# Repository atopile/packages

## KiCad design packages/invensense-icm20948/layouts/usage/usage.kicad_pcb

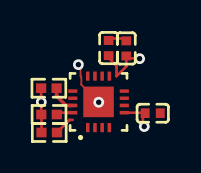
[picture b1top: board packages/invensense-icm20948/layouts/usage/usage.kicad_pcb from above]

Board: 2 copper layers, 7 parts (0 on the bottom side), 7 nets.

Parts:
C1, C3: 1±10.0%F; C0402
C2: {8.999..1.1}F; C0402
R1, R2, R3: 10000±1.0%Ω; R0402
U1: QFN-24_L3.0-W3.0-P0.40-BL-EP

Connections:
RESV: U1.19, U1.20
SCL: R2.2, U1.23
SDA: R3.2, U1.24
hv: C3.1, R1.1, R2.1, R3.1, U1.8
lv: C1.2, C2.2, C3.2, U1.9, U1.18, U1.25
nCS: R1.2, U1.22
power_core_filter-power-hv: C1.1, C2.1, U1.13

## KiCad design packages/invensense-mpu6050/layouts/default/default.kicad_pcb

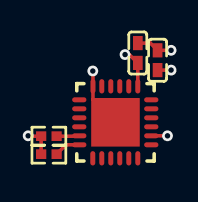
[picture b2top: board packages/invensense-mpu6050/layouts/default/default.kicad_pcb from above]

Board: 2 copper layers, 5 parts (0 on the bottom side), 5 nets.

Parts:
C1, C2: 1±10.0%F; C0402
R1, R2: 10000±1.0%Ω; R0402
U1: QFN-24_L4.0-W4.0-P0.50-BL-EP2.7

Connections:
SCL: R1.1, U1.23
SDA: R2.1, U1.24
decoupling_caps[0]-power-hv: C1.1, U1.13
hv: C2.1, R1.2, R2.2, U1.8
lv: C1.2, C2.2, U1.9, U1.18, U1.25

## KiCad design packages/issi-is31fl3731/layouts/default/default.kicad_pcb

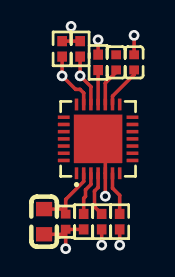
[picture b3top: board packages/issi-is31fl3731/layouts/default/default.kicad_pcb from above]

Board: 2 copper layers, 11 parts (0 on the bottom side), 10 nets.

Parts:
C1, C4, C5: 1±10.0%F; C0402
C2: {8.999..1.1}F; C0603
R1: 20000±1.0%Ω; R0402
R2, R3, R6: 10000±1.0%Ω; R0402
R4, R5: 4700±1.0%Ω; R0402
U1: QFN-28_L4.0-W4.0-P0.40-BL-EP

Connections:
AD: R2.1, U1.18
INTB: R3.1, U1.4
R_EXT: R1.1, U1.6
SCL: R4.1, U1.20
SDA: R5.1, U1.19
SDB: R6.1, U1.3
decoupling_capacitor_small-power-hv: C2.1, C4.1, R3.2, R4.2, R5.2, U1.2
filter_capacitor-power-hv: C5.1, U1.16
filter_capacitor-power-lv: C2.2, C4.2, C5.2, R1.2, R2.2, R6.2, U1.5, U1.29
lv: C1.2, U1.17

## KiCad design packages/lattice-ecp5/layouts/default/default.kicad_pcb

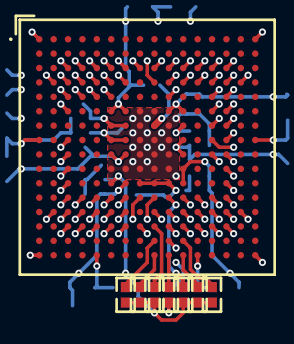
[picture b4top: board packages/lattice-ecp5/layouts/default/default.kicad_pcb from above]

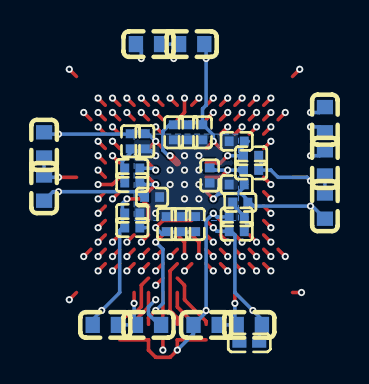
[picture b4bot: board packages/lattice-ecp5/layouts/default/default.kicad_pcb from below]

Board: 4 copper layers, 41 parts (33 on the bottom side), 17 nets.

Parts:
C1, C4, C5, C6, C7, C8, C9, C10, C24, C25, C26: 0F; C0603
C2, C3, C11, C12, C13, C14, C15, C16, C17, C18, C19, C20, C21, C22, C23, C27, C28, C29, C30, C31, C32: 0F; C0402
L1: L0402
R1, R2, R3, R4, R5, R6, R7: 4700Ω; R0402
U1: CABGA-256_L14.0-W14.0-R16-C16-P0.80-TL

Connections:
DONE: R3.1, U1.P9
GND: C1.2, C2.1, C3.1, C4.2, C5.2, C6.2, C7.2, C8.2, C9.2, C10.2, C11.2, C12.2, C13.2, C14.2, C15.2, C16.2, C17.2, C18.2, C19.2, C20.2, C21.2, C22.2, C23.2, C24.2, C25.2, C26.2, C27.1, C28.1, C29.1, C30.1, C31.1, C32.1, R7.2, U1.A1, U1.A16, U1.D2, U1.D15, U1.F8, U1.F9, U1.G8, U1.G10, U1.H1, U1.H8, U1.H9, U1.H10, U1.H16, U1.J8, U1.J9, U1.J10, U1.K6, U1.K7, U1.K8, U1.K9, U1.K10, U1.N2, U1.N15, U1.T1, U1.T5, U1.T12, U1.T16
INITN: R2.1, U1.T9
PROGRAMN: R1.1, U1.R9
TCK: R7.1, U1.T10
TDI: R4.1, U1.R11
TDO: R6.1, U1.M10
TMS: R5.1, U1.T11
hv: C1.1, C2.2, C3.2, L1.2, U1.G11, U1.L7
power_core-hv: C24.1, C25.1, C26.1, C27.2, C28.2, C29.2, C30.2, C31.2, C32.2, U1.G6, U1.G7, U1.G9, U1.L8, U1.L9, U1.L10
power_vccio[0]-hv: C4.1, C11.1, C12.1, U1.F6, U1.F7
power_vccio[1]-hv: C5.1, C13.1, C14.1, U1.F10, U1.F11
power_vccio[2]-hv: C6.1, C15.1, C16.1, U1.H11, U1.J11
power_vccio[3]-hv: C7.1, C17.1, C18.1, U1.K11, U1.L11
power_vccio[6]-hv: C8.1, C19.1, C20.1, U1.J6, U1.J7
power_vccio[7]-hv: C9.1, C21.1, C22.1, U1.H6, U1.H7
power_vccio[8]-hv: C10.1, C23.1, R1.2, R2.2, R3.2, R4.2, R5.2, R6.2, U1.L6

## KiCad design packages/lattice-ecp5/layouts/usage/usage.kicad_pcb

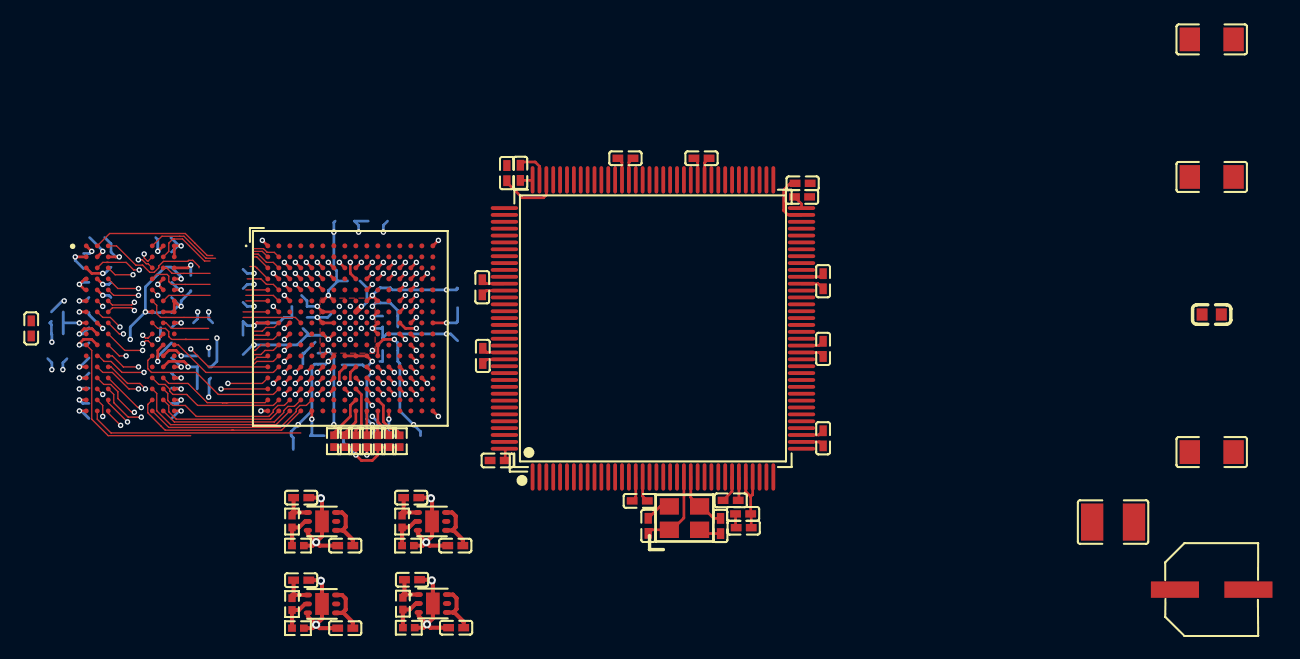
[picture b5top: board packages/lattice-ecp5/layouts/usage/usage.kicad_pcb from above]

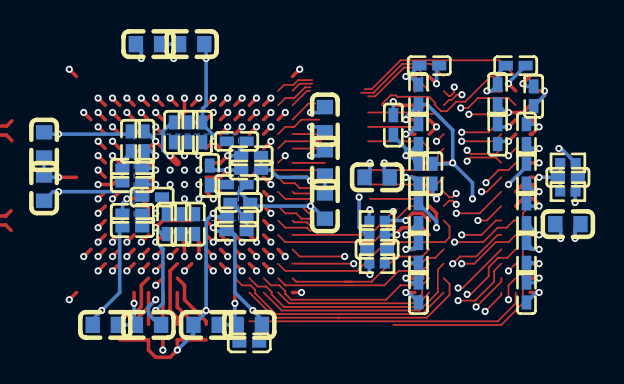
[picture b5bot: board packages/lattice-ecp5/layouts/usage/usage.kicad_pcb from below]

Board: 4 copper layers, 116 parts (60 on the bottom side), 64 nets.

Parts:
C1, C4, C5, C6, C7, C8, C9, C10, C24, C25, C26, C61, C67, C68: 10µF ±20% 6.3V X5R; C0603
C2, C3, C27, C28, C29, C30, C31, C32, C65, C66, C69, C70, C71, C72, C73, C74, C75, C76, C77, C78, C79, C80, C81, C82, C83, C84, C85, C86: 100nF ±10% 6.3V X7R; C0402
C11, C12, C13, C14, C15, C16, C17, C18, C19, C20, C21, C22, C23: 100nF ±10% 10V X5R; C0402
C33, C34, C35, C36, C37, C38, C39, C40, C57: 1µF ±10% 25V X5R; C0402
C41, C42, C43, C44, C45, C46, C47, C48, C49, C50, C51, C52, C58: 100nF ±10% 16V X7R; C0402
C53, C54: 18pF ±5% 50V C0G; C0402
C55, C56: 2.2µF ±20% 6.3V X5R; C0402
C59: 47µF ±10% 6.3V X7R; C1210
C60, C62, C63: 22µF ±20% 6.3V X5R; C1206
C64: CAP-SMD_BD6.3-L6.6-W6.6-LS7.6-FD
L1, L2: L0402
R1, R2, R3, R4: 1kΩ ±1% 62.5mW; R0402
R5: 240Ω ±1% 62.5mW; R0402
R6, R7, R8, R9, R10, R11, R12: 4.7kΩ ±1% 62.5mW; R0402
R13, R14, R15, R18, R19: 10kΩ ±1% 62.5mW; R0402
R16: 15kΩ ±1% 62.5mW; R0402
R17: 3kΩ ±1% 62.5mW; R0402
R20: 47kΩ ±1% 62.5mW; R0402
U1: TFBGA-96_L13.0-W7.5-R16-C6-P0.80-TL
U2: CABGA-256_L14.0-W14.0-R16-C16-P0.80-TL
U3, U4, U5, U6: WSON-6_L2.0-W2.0-P0.65-TL-EP
U7: LQFP-144_L20.0-W20.0-P0.50-LS22.0-BL
X1: OSC-SMD_4P-L3.2-W2.5-BL_SIT8008BI

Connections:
1V1: C24.1, C25.1, C26.1, C27.1, C28.1, C29.1, C30.1, C31.1, C32.1, C34.1, C59.1, R14.1, U2.G6, U2.G7, U2.G9, U2.L8, U2.L9, U2.L10, U3.1
1V35: C8.1, C9.1, C19.1, C20.1, C21.1, C22.1, C36.1, C60.1, C67.1, C69.1, C70.1, C71.1, C72.1, C73.1, C74.1, C75.1, C76.1, C77.1, L2.1, R2.1, R4.1, R16.1, U1.A1, U1.A8, U1.C1, U1.C9, U1.D2, U1.E9, U1.F1, U1.H2, U1.H9, U2.H6, U2.H7, U2.J6, U2.J7, U4.1
1V35_int: C68.1, C78.1, C79.1, C80.1, C81.1, C82.1, C83.1, C84.1, C85.1, C86.1, L2.2, U1.B2, U1.D9, U1.G7, U1.K2, U1.K8, U1.N1, U1.N9, U1.R1, U1.R9
2V5: C38.1, C62.1, L1.1, R18.1, U5.1
3V3: C4.1, C5.1, C6.1, C7.1, C10.1, C11.1, C12.1, C13.1, C14.1, C15.1, C16.1, C17.1, C18.1, C23.1, C33.1, C35.1, C40.1, C41.1, C42.1, C43.1, C44.1, C45.1, C46.1, C47.1, C48.1, C49.1, C50.1, C51.1, C52.1, C57.1, C58.1, C63.1, R6.2, R7.2, R8.2, R9.2, R10.2, R11.2, R20.1, U2.F6, U2.F7, U2.F10, U2.F11, U2.H11, U2.J11, U2.K11, U2.L6, U2.L11, U3.4, U3.6, U4.4, U4.6, U6.1, U7.17, U7.30, U7.32, U7.33, U7.39, U7.52, U7.62, U7.72, U7.84, U7.95, U7.108, U7.121, U7.131, U7.144
5V0: C37.1, C39.1, C64.1, U5.4, U5.6, U6.4, U6.6
CKE: U1.K9, U2.M2
DONE: R8.1, U2.P9
GND: C1.2, C2.2, C3.2, C4.2, C5.2, C6.2, C7.2, C8.2, C9.2, C10.2, C11.2, C12.2, C13.2, C14.2, C15.2, C16.2, C17.2, C18.2, C19.2, C20.2, C21.2, C22.2, C23.2, C24.2, C25.2, C26.2, C27.2, C28.2, C29.2, C30.2, C31.2, C32.2, C33.2, C34.2, C35.2, C36.2, C37.2, C38.2, C39.2, C40.2, C41.2, C42.2, C43.2, C44.2, C45.2, C46.2, C47.2, C48.2, C49.2, C50.2, C51.2, C52.2, C53.2, C54.2, C55.2, C56.2, C57.2, C58.2, C59.2, C60.2, C62.2, C63.2, C64.2, C65.2, C66.2, C67.2, C68.2, C69.2, C70.2, C71.2, C72.2, C73.2, C74.2, C75.2, C76.2, C77.2, C78.2, C79.2, C80.2, C81.2, C82.2, C83.2, C84.2, C85.2, C86.2, R1.2, R3.2, R5.2, R12.2, R13.2, R15.2, R17.2, R19.2, U1.A9, U1.B1, U1.B3, U1.B9, U1.D1, U1.D8, U1.E1, U1.E2, U1.E8, U1.F9, U1.G1, U1.G8, U1.G9, U1.J2, U1.J8, U1.M1, U1.M9, U1.P1, U1.P9, U1.T1, U1.T9, U2.A1, U2.A16, U2.D2, U2.D15, U2.F8, U2.F9, U2.G8, U2.G10, U2.H1, U2.H8, U2.H9, U2.H10, U2.H16, U2.J8, U2.J9, U2.J10, U2.K6, U2.K7, U2.K8, U2.K9, U2.K10, U2.N2, U2.N15, U2.T1, U2.T5, U2.T12, U2.T16, U3.3, U3.7, U4.3, U4.7, U5.3, U5.7, U6.3, U6.7, U7.16, U7.31, U7.38, U7.51, U7.61, U7.83, U7.94, U7.107, U7.120, U7.130, X1.2, X1.4
INITN: R7.1, U2.T9
PL26C: U1.J3, U2.M1
PL32D: U1.K3, U2.M3
PL35D: U1.L2, U2.N3
PL44C: U1.L3, U2.M5
PROGRAMN: R6.1, U2.R9
TCK: R12.1, U2.T10
TDO: R11.1, U2.M10
TMS: R10.1, U2.T11
ZQ: R5.1, U1.L8
ddr_a0: U1.N3, U2.N4
ddr_a1: U1.P7, U2.T3
ddr_a2: U1.P3, U2.P4
ddr_a3: U1.N2, U2.P3
ddr_a4: U1.P8, U2.R3
ddr_a5: U1.P2, U2.N5
ddr_a6: U1.R8, U2.T2
ddr_a7: U1.R2, U2.P6
ddr_a8: U1.T8, U2.R4
ddr_a9: U1.R3, U2.P5
ddr_a10: U1.L7, U2.P2
ddr_a11: U1.R7, U2.T4
ddr_a12: U1.N7, U2.R2
ddr_a13: U1.T3, U2.N6
ddr_a14: U1.T7, U2.R5
ddr_ba0: U1.M2, U2.N1
ddr_ba1: U1.N8, U2.R1
ddr_ba2: U1.M3, U2.P1
ddr_dql0: U1.E3, U2.J5
ddr_dql1: U1.F7, U2.H4
ddr_dql2: U1.F2, U2.J4
ddr_dql3: U1.F8, U2.H5
ddr_dql4: U1.H3, U2.H3
ddr_dql5: U1.H8, U2.G2
ddr_dql6: U1.G2, U2.G3
ddr_dql7: U1.H7, U2.F1
ddr_dqu0: U1.D7, U2.K2
ddr_dqu1: U1.C3, U2.J2
ddr_dqu2: U1.C8, U2.K1
ddr_dqu3: U1.C2, U2.J1
ddr_dqu4: U1.A7, U2.K3
ddr_dqu5: U1.A2, U2.H2
ddr_dqu6: U1.B8, U2.J3
ddr_dqu7: U1.A3, U2.G1
feedback_divider-output-VDIV_OUTPUT-0: R13.1, R14.2, U3.2
feedback_divider-output-VDIV_OUTPUT-1: R15.1, R16.2, U4.2
feedback_divider-output-VDIV_OUTPUT-2: R17.1, R18.2, U5.2
feedback_divider-output-VDIV_OUTPUT-3: R19.1, R20.2, U6.2
hse-XIN: C53.1, U7.23, X1.1
hse-XOUT: C54.1, U7.24, X1.3
model-jtag-TDI: R9.1, U2.R11
power_vcap-VCC: C55.1, C56.1, U7.71, U7.106
power_vccaux_filtered-VCC: C1.1, C2.1, C3.1, L1.2, U2.G11, U2.L7
vrefca-VCC: C65.1, R1.1, R2.2, U1.M8
vrefdq-VCC: C66.1, R3.1, R4.2, U1.H1

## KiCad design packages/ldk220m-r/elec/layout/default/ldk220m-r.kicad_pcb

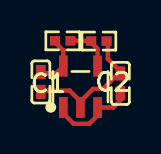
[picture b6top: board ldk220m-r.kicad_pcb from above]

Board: 2 copper layers, 5 parts (0 on the bottom side), 4 nets.

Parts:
C1, C2: 1µF ±10% 25V X5R; C0402-b3ef17
R1: 18kΩ ±1% 62.5mW; R0402-56259e
R2: 10kΩ ±1% 62.5mW; R0402-56259e
U1: SOT-23-5_L3.0-W1.7-P0.95-LS2.8-BL

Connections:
ADJ_NC: R1.2, R2.1, U1.4
IN: C1.1, U1.1, U1.3
OUT: C2.1, R1.1, U1.5
gnd: C1.2, C2.2, R2.2, U1.2
